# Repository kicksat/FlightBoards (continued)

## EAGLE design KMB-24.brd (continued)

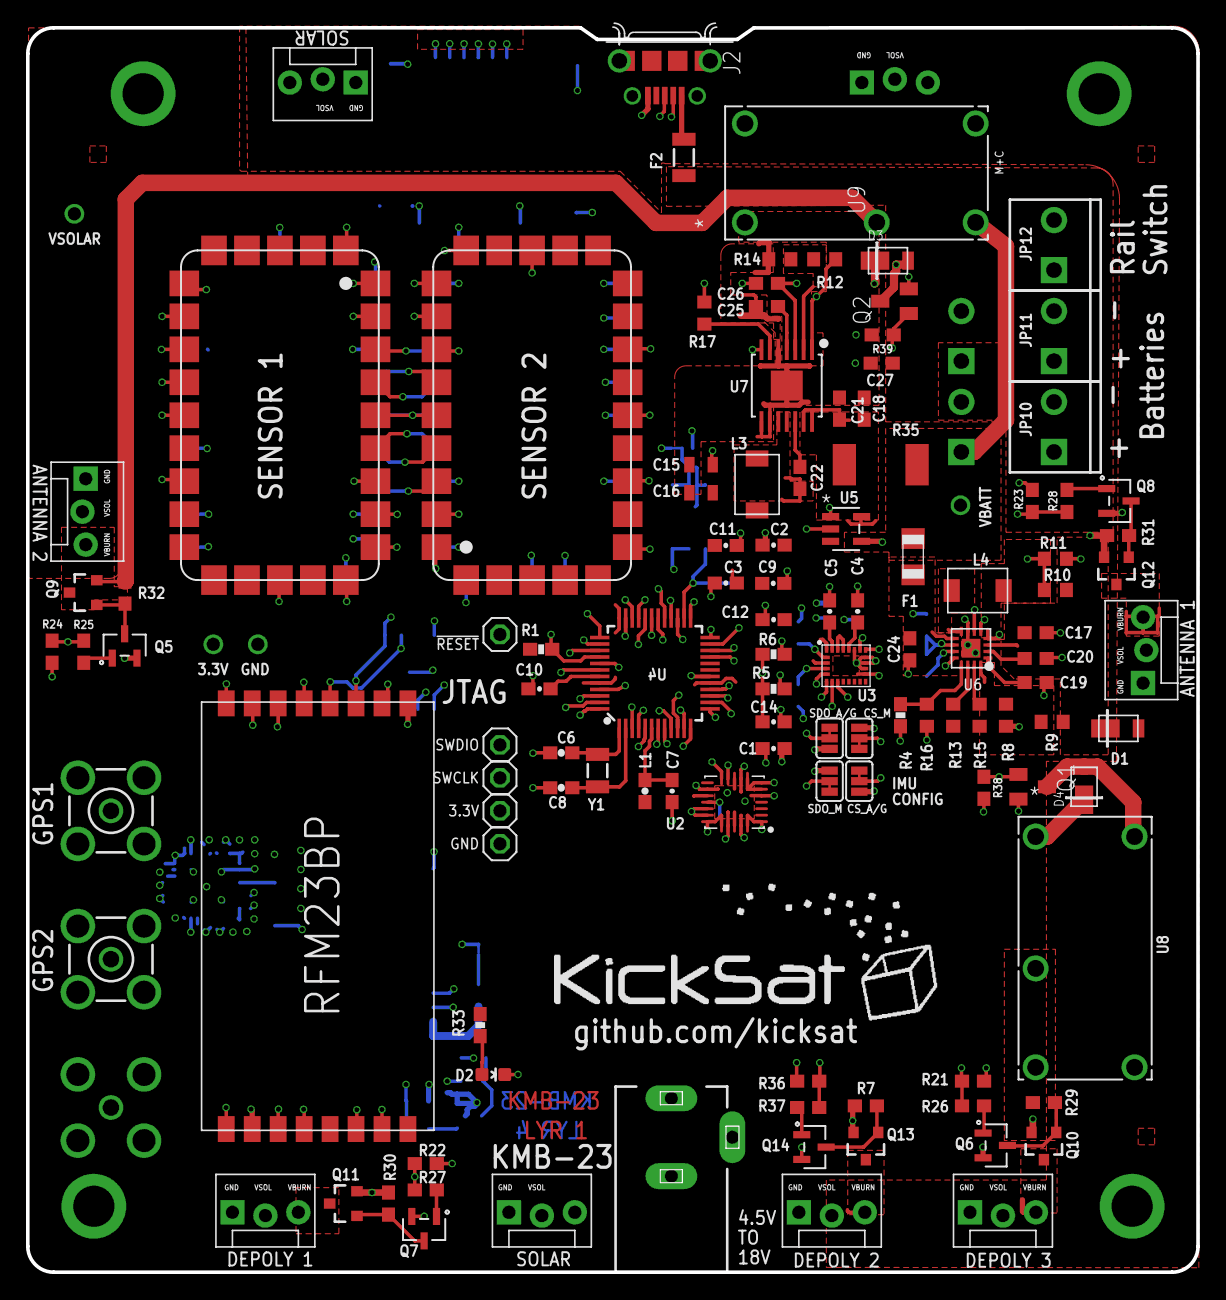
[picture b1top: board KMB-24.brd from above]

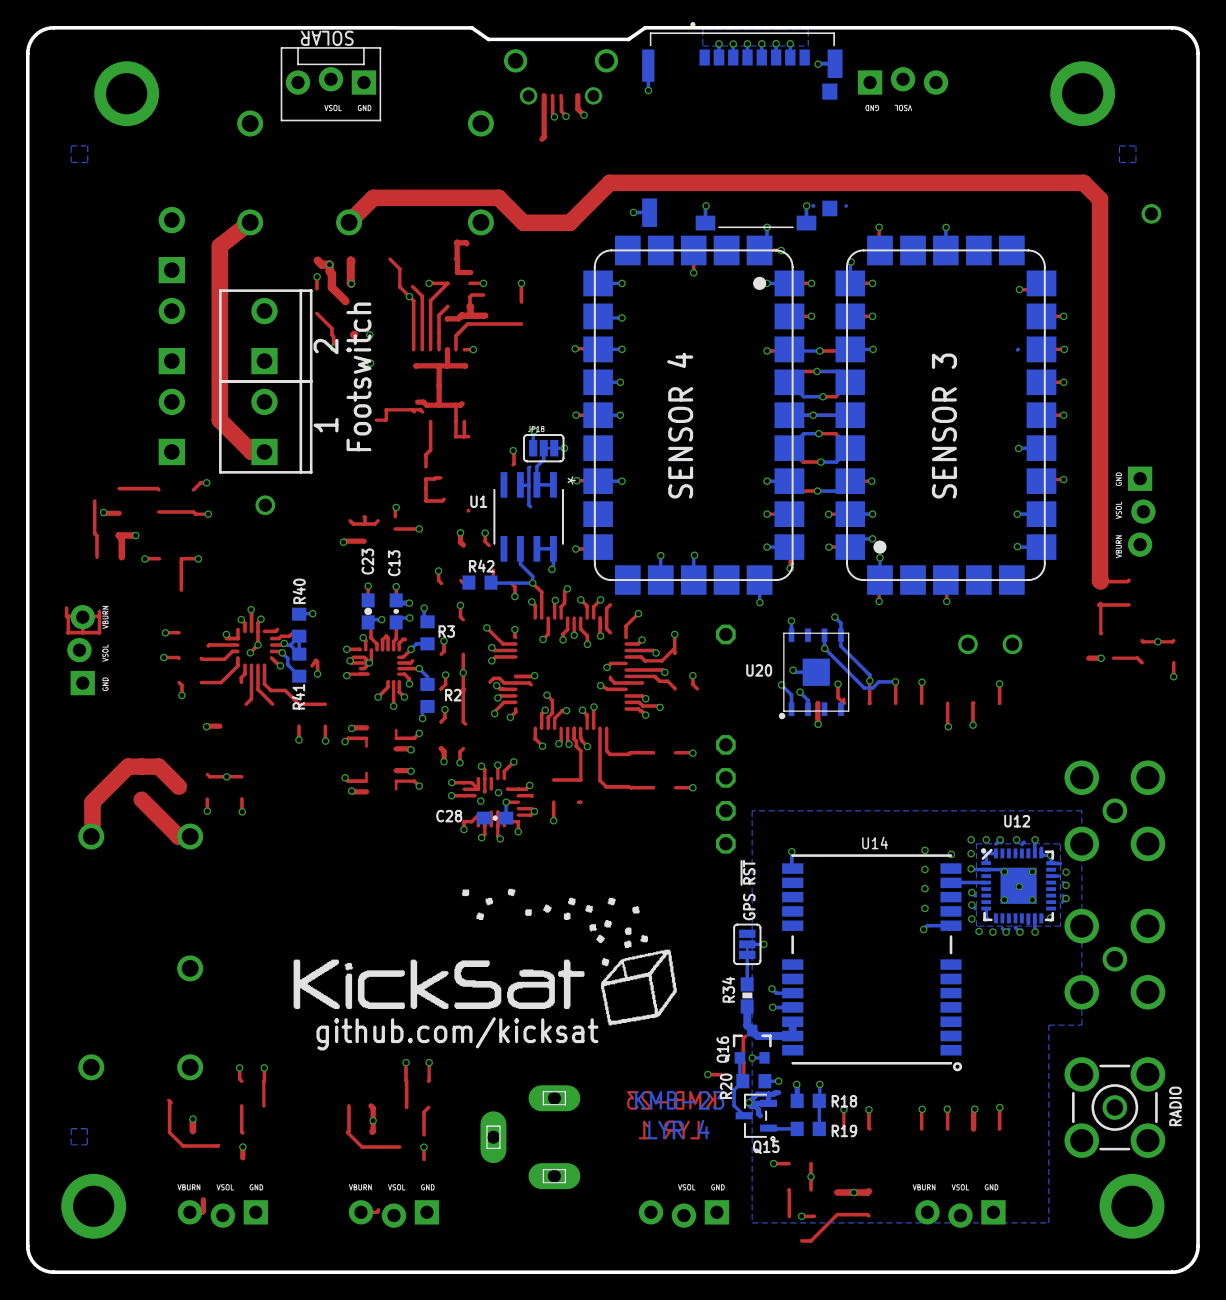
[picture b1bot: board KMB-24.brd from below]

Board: 4 copper layers, 90.2 x 95.9 mm, 148 parts (28 on the bottom side), 106 nets.

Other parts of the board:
L5: KICKSAT_LOGO

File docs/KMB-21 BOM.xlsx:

OSH ORDER 2018-06-04 |  |  | KMB-21.sch at 6/6/2018 5:23 PM
 |  |  |  |  |  | (DK 2018-04-05) | (2*2.1 rounded) | (DK 2018-06-07)
Qty | Value | Device | Package | Parts | Description | Inventory | Total Needed | New Order | Comments
3 | 22uF | 22UF-0805-6.3V-20% | 805 | C15, C16, C24 | 22ÂµF ceramic capacitors | 6 | 13 | 15
4 | 10uF | 10UF-0603-6.3V-20% | 603 | C1, C17, C18, C21 | 10.0ÂµF ceramic capacitors | 95 | 17
3 | 2.2uF | 2.2UF-0603-10V-20% | 603 | C19, C20, C27 | 2.2ÂµF ceramic capacitors | 98 | 13
12 | 0.1uF | 0.1UF-25V(+80/-20%)(0603) | 0603-CAP | C2, C3, C5, C7, C9, C10, C11, C12, C13, C14, C22, C23 | CAP-00810 | 85 | 50
1 | 3.3nF | 3.3NF-0603-100V-10% | 603 | C25 | 3.3nF ceramic capacitors | 8 | 4
1 | 1.0uF | 1.0UF-0603-16V-10% | 603 | C26 | 1ÂµF ceramic capacitors | 98 | 4
1 | 10nF | 10NF/10000PF-50V-10%(0603) | 0603-CAP | C4 | CAP-00867 | 99 | 4
2 | 15pF | 15PF-50V-5%(0603) | 0603-CAP@1 | C6, C8 | CAP-07881 | 98 | 8
1 | DFLS130L | DFLS130L | PWRDI-123 | D1 |  | 9 | 4
1 | GREEN | LED-GREEN0603 | LED-0603 | D2 | Various green LEDs | 0 | 4 | 10
1 | 1206L200 | PTCFUSE1206 | 1206 | F1 | PTC Fuse | 9 | 4
1 | 500mA | PTCSMD | PTC-1206 | F2 | Resettable Fuse PTC | 9 | 4
1 | 503182-1852 | 503182-1852 | MOLEX_503182-1852 | J1 | Conn Micro SD Card M 8 POS 1.09mm Solder RA SMD Embossed T/R 0.5A/Contact | 0 | 4 | 10
1 | 10118194-0001LF | 10118194-0001LF | FRAMATOME_10118194-0001LF | J2 | Conn Micro USB Type B RCP 5 POS 0.65mm Solder RA SMD 5 Terminal 1 Port T/R | 0 | 4 | 25
1 | DCJ0303 | DCJ0303 | DCJ0303 | J3 | DC POWER JACK | 0 | 4 | 10
5 | M023.5MM_LOCK | M023.5MM_LOCK | SCREWTERMINAL-3.5MM-2_LOCK | JP10, JP11, JP12, JP13, JP16 | Standard 2-pin 0.1" header. Use with | 45 | 21
7 |  | M03POLAR_LOCK | MOLEX-1X3_LOCK | JP5, JP6, JP8, JP9, JP14, JP15, JP17 | Header 3 | 100 | 29
1 | FB - 30Ohm | INDUCTOR0603 | 603 | L1 | Inductors | 8 | 4
1 | 3.3uH | IND1812 | 1812 | L3 |  | 2 | 4 | 0 | Decent inductors are restricted on digikey? Need to go to Mouser?
1 | 56uH | IND1812 | 1812 | L4 |  | 4 | 4
7 | IRLML2803 | IRLML2803TRPBF | SOT-23 | Q1, Q2, Q3, Q5, Q6, Q7, Q8 |  | 5 | 29 | 50
5 | IRLML5103 | MOSFET-PCHANNEL | SOT23-3 | Q4, Q9, Q10, Q11, Q12 | Generic PMOSFET | 4 | 21 | 50
8 | 10K | 10KOHM-1/10W-1%(0603)0603 | 0603-RES | R1, R4, R18, R21, R22, R23, R24, R34 | RES-00824 | 0 | 34 | 100
1 | 330K | R-US_R0603 | R0603 | R10 | RESISTOR, American symbol | 99 | 4
1 | 43K | R-US_R0603 | R0603 | R11 | RESISTOR, American symbol | 99 | 4
1 | 73.2K | R-US_R0603 | R0603 | R12 | RESISTOR, American symbol | 0 | 4 | 20
1 | 470k | R-US_R0603 | R0603 | R13 | RESISTOR, American symbol | 99 | 4
1 | 22.1k | R-US_R0603 | R0603 | R14 | RESISTOR, American symbol | 0 | 4 | 20
1 | 6.04K | R-US_R0603 | R0603 | R16 | RESISTOR, American symbol | 99 | 4
8 | 4.7k | R-US_R0603 | R0603 | R2, R3, R15, R19, R25, R26, R27, R28 | RESISTOR, American symbol | 0 | 34 | 100
1 | 3.3K | R-US_R0603 | R0603 | R20 | RESISTOR, American symbol | 99 | 4
6 | 100k | RESISTOR0603 | 603 | R8, R17, R29, R30, R31, R32 | Generic Resistor Package | 0 | 25 | 100
1 | 330 | 330OHM1/10W1%(0603) | 0603-RES | R33 | RES-00818 | 0 | 4 | 100
1 | 2.5000000000000001E-2 | R-US_R2512 | R2512 | R35 | RESISTOR, American symbol | 0 | 4 | 5
1 | 110K | 10KOHM-1/10W-1%(0603)0603 | 0603-RES | R5 | RES-00824 | 99 | 4
1 | 316K | 10KOHM-1/10W-1%(0603)0603 | 0603-RES | R6 | RES-00824 | 99 | 4
1 | 40.9K | R-US_R0603 | R0603 | R9 | RESISTOR, American symbol | 0 | 4 | 100
1 | MAX706R | MAX708RESA-T | SO8 | U1 |  | 0 | 4 | 5
1 | EP2W+ | EP2W+ | QFN32-5X5MM | U12 |  | 0 | 4 | 0
1 | RFM23BP | RFM23BP | RFM23BP | U13 | HopeRF RFM23BP | 0 | 4 | 0
1 | S1216V8 | S1216V8 | S1216_24PIN_PACKAGE | U14 |  | 0 | 4 | 0
1 | MR25H40 | MR25H40 | DFN-8 | U2 |  | 0 | 4 | 2 | Expensive
1 | LSM9DS1 | LSM9DS1 | LGA24-8X4 | U3 | LSM9DS1 3D accelerometer, gyroscope & magnetometer | 9 | 4
1 | ATSAMD21G-A | ATSAMD21G-A | TQFP-48 | U4 | Atmel SAMD21G SMART ARM-Based Microcontroller | 8 | 4
1 | MAX4372TEUK+T | MAX4372TEUK+T | 21-0057F | U5 |  | 8 | 4
1 | LTC4121-4.2 | LTC4121-4.2 | QFN-16-PAD | U6 |  | 4 | 4
1 | TPS54226PWPRPWP14_2P31X2P46-L | TPS54226PWPRPWP14_2P31X2P46-L | PWP14_2P31X2P46-L | U7 |  | 6 | 4
2 | PE014006 | PE014005 | RELAY5-PE_CO | U8, U9 |  | 0 | 8 | 10
3 | BU-SMA-V | BU-SMA-V | BU-SMA-V | X1, X2, X3 | FEMALE SMA CONNECTOR | 7 | 13 | 0
1 | 32.768kHz | CRYSTAL3.2X1.5MM | CRYSTAL-SMD-3.2X1.5MM | Y1 | Various standard crystals. Proven footprints. | 9 | 4
NON PCB ITEMS
3 | 4GB | S304TLN7B-U1000-3 |  |  | Flash Memory Card, MicroSDHC Card, UHS-1, Class 10, 4 GB, U331 Series | 0 | 1 | 0 | 56 ea from Newark http://www.newark.com/delkin-devices/s304tln7b-u1000-3/memory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

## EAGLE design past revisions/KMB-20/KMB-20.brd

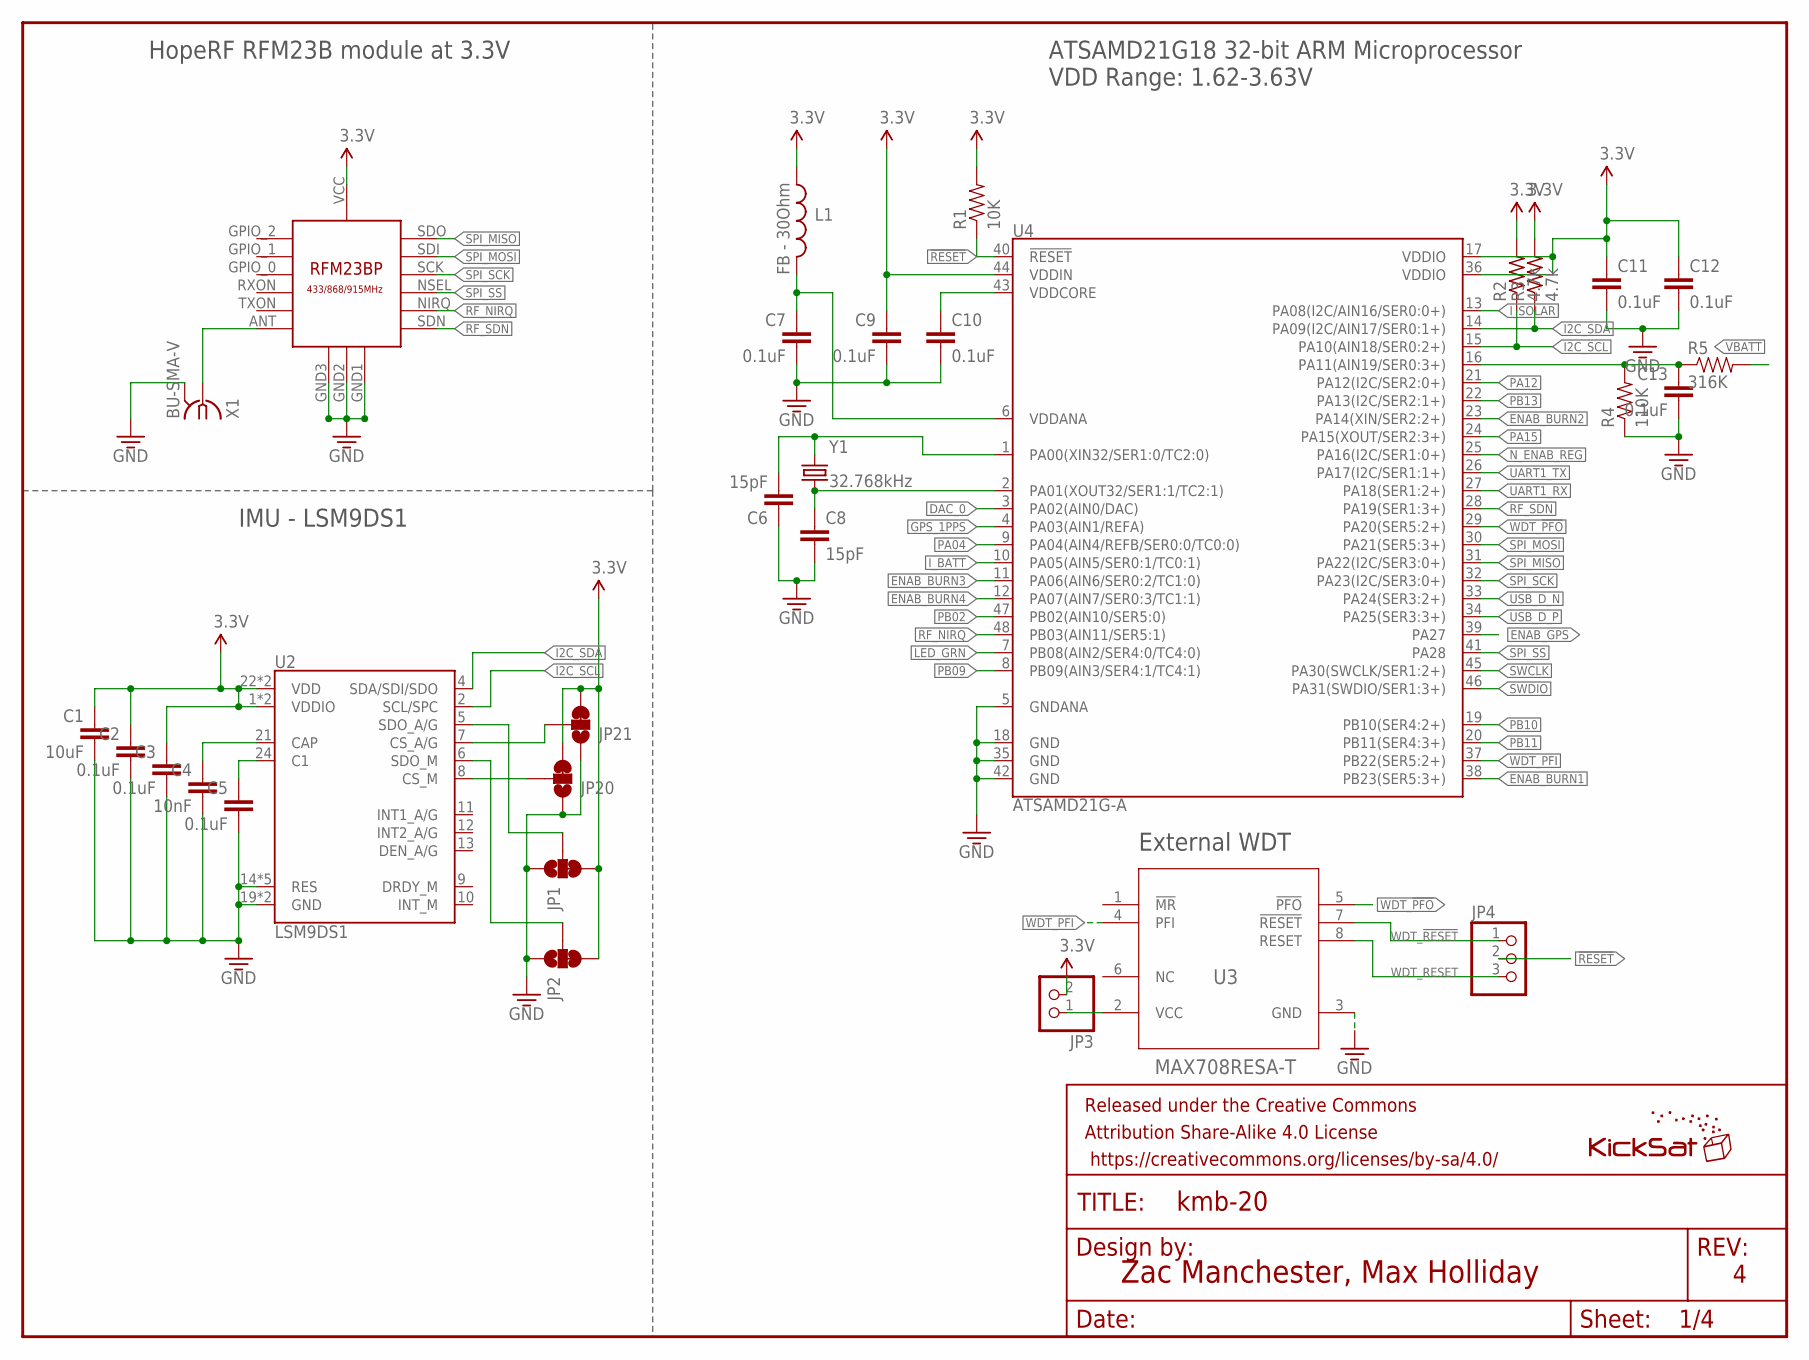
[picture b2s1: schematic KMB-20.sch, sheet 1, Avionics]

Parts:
C1: 10uF; 0603-CAP
C2, C3, C5, C7, C9, C10, C11, C12, C13: 0.1uF; 0603-CAP
C4: 10nF; 0603-CAP
C6, C8: 15pF; 0603-CAP@1
FRAME1: FRAME-LETTER; CREATIVE_COMMONS
JP1, JP2, JP20, JP21: JUMPER-PAD-3-2OF3_NC_BY_TRACE_SMALL; PAD-JUMPER-3-2OF3_NC_BY_TRACE_YES_SILK_FULL_BOX
JP3: PINHD-1X2; 1X02
JP4: PINHD-1X3; 1X03
L1: FB - 30Ohm; 0603
L2: KICKSAT_LOGO
R1: 10K; 0603-RES
R2, R3: 4.7k; R0603
R4: 110K; 0603-RES
R5: 316K; 0603-RES
U1: RFM23BP
U2: LSM9DS1; LGA24-8X4
U3: MAX708RESA-T; SO8
U4: ATSAMD21G-A; TQFP-48
X1: BU-SMA-V
Y1: 32.768kHz; CRYSTAL-SMD-3.2X1.5MM

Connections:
3.3V: C1.1, C2.1, C3.1, C9.1, C11.1, C12.1, JP1.3, JP2.3, JP3.2, JP20.3, JP21.3, L1.1, R1.2, R2.2, R3.2, U1.VCC, U2.1 (VDDIO), U2.3 (VDDIO), U2.22 (VDD), U2.23 (VDD), U4.17 (VDDIO), U4.36 (VDDIO), U4.44 (VDDIN); also elsewhere on the board
!RESET: JP4.2, R1.1, U4.40 (!RESET!); also elsewhere on the board
DAC_0: U4.3 (PA02(AIN0/DAC)); also elsewhere on the board
ENAB_BURN1: U4.38 (PB23(SER5:3+)); also elsewhere on the board
ENAB_BURN2: U4.23 (PA14(XIN/SER2:2+)); also elsewhere on the board
ENAB_BURN3: U4.11 (PA06(AIN6/SER0:2/TC1:0)); also elsewhere on the board
ENAB_BURN4: U4.12 (PA07(AIN7/SER0:3/TC1:1)); also elsewhere on the board
ENAB_GPS: U4.39 (PA27); also elsewhere on the board
GND: C1.2, C2.2, C3.2, C4.2, C5.2, C6.1, C7.2, C8.2, C9.2, C10.2, C11.2, C12.2, C13.2, JP1.1, JP2.1, JP20.1, JP21.1, R4.1, U1.GND1, U1.GND2, U1.GND3, U2.14 (RES), U2.15 (RES), U2.16 (RES), U2.17 (RES), U2.18 (RES), U2.19 (GND), U2.20 (GND), U3.3 (GND), U4.5 (GNDANA), U4.18 (GND), U4.35 (GND), U4.42 (GND), X1.2, X1.3 (2), X1.4 (2), X1.5 (2); also elsewhere on the board
GPS_1PPS: U4.4 (PA03(AIN1/REFA)); also elsewhere on the board
I2C_SCL: R2.1, U2.2 (SCL/SPC), U4.15 (PA10(AIN18/SER0:2+)); also elsewhere on the board
I2C_SDA: R3.1, U2.4 (SDA/SDI/SDO), U4.14 (PA09(I2C/AIN17/SER0:1+)); also elsewhere on the board
I2C_SDOA/G: JP1.2, U2.5 (SDO_A/G)
I_BATT: U4.10 (PA05(AIN5/SER0:1/TC0:1)); also elsewhere on the board
I_SOLAR: U4.13 (PA08(I2C/AIN16/SER0:0+)); also elsewhere on the board
LED_GRN: U4.7 (PB08(AIN2/SER4:0/TC4:0)); also elsewhere on the board
unnamed: C4.1, U2.21 (CAP)
unnamed: C5.1, U2.24 (C1)
unnamed: JP3.1, U3.2 (VCC)
unnamed: C7.1, L1.2, U4.6 (VDDANA)
unnamed: U1.ANT, X1.1
unnamed: JP2.2, U2.6 (SDO_M)
unnamed: JP20.2, U2.8 (CS_M)
unnamed: JP21.2, U2.7 (CS_A/G)
unnamed: C6.2, U4.1 (PA00(XIN32/SER1:0/TC2:0)), Y1.P$2 (2)
unnamed: C8.1, U4.2 (PA01(XOUT32/SER1:1/TC2:1)), Y1.P$1 (1)
unnamed: C13.1, R4.2, R5.1, U4.16 (PA11(AIN19/SER0:3+))
N_ENAB_REG: U4.25 (PA16(I2C/SER1:0+)); also elsewhere on the board
PA04: U4.9 (PA04(AIN4/REFB/SER0:0/TC0:0))
PA12: U4.21 (PA12(I2C/SER2:0+)); also elsewhere on the board
PA15: U4.24 (PA15(XOUT/SER2:3+))
PB02: U4.47 (PB02(AIN10/SER5:0)); also elsewhere on the board
PB09: U4.8 (PB09(AIN3/SER4:1/TC4:1)); also elsewhere on the board
PB10: U4.19 (PB10(SER4:2+)); also elsewhere on the board
PB11: U4.20 (PB11(SER4:3+)); also elsewhere on the board
PB13: U4.22 (PA13(I2C/SER2:1+))
RF_NIRQ: U1.NIRQ, U4.48 (PB03(AIN11/SER5:1))
RF_SDN: U1.SDN, U4.28 (PA19(SER1:3+))
SPI_MISO: U1.SDO, U4.31 (PA22(I2C/SER3:0+))
SPI_MOSI: U1.SDI, U4.30 (PA21(SER5:3+))
SPI_SCK: U1.SCK, U4.32 (PA23(I2C/SER3:0+))
SPI_SS: U1.NSEL, U4.41 (PA28)
SWCLK: U4.45 (PA30(SWCLK/SER1:2+)); also elsewhere on the board
SWDIO: U4.46 (PA31(SWDIO/SER1:3+)); also elsewhere on the board
UART1_RX: U4.27 (PA18(SER1:2+)); also elsewhere on the board
UART1_TX: U4.26 (PA17(I2C/SER1:1+)); also elsewhere on the board
USB_D_N: U4.33 (PA24(SER3:2+)); also elsewhere on the board
USB_D_P: U4.34 (PA25(SER3:3+)); also elsewhere on the board
VBATT: R5.2; also elsewhere on the board
VDDCORE3: C10.1, U4.43 (VDDCORE)
WDT_!PFO: U3.5 (!PFO), U4.29 (PA20(SER5:2+))
WDT_!RESET: JP4.1, U3.7 (!RESET)
WDT_PFI: U3.4 (PFI), U4.37 (PB22(SER5:2+))
WDT_RESET: JP4.3, U3.8 (RESET)

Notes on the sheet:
Zac Manchester, Max Holliday
ATSAMD21G18 32-bit ARM Microprocessor VDD Range: 1.62-3.63V
HopeRF RFM23B module at 3.3V
IMU - LSM9DS1
External WDT

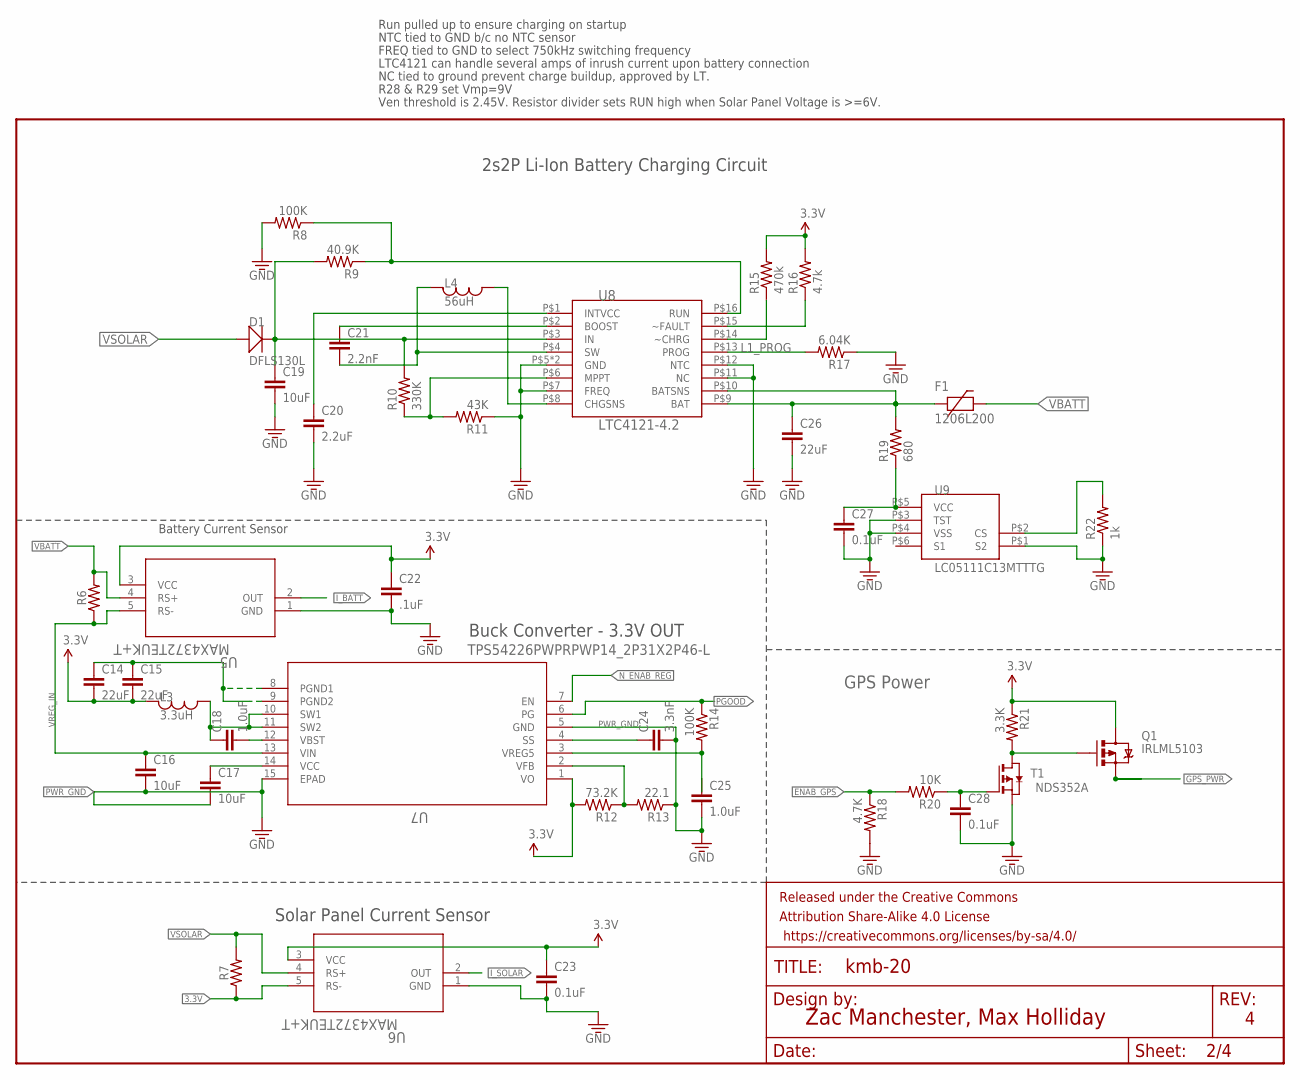
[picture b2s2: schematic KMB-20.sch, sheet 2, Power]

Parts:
C14, C15: 22uF; 0805
C16, C17, C19: 10uF; 0603
C18, C25: 1.0uF; 0603
C20: 2.2uF; 0603
C21: 2.2nF; 0603
C22: .1uF; 0603-CAP@1
C23, C27, C28: 0.1uF; 0603
C24: 3.3nF; 0603
C26: 22uF; 0603
D1: DFLS130L; PWRDI-123
F1: 1206L200; 1206
FRAME2: FRAME-LETTER; CREATIVE_COMMONS
L3: 3.3uH; 1812
L4: 56uH; 1812
Q1: IRLML5103; SOT23-3
R6, R7: 0603
R8, R14: 100K; R0603
R9: 40.9K; R0603
R10: 330K; R0603
R11: 43K; R0603
R12: 73.2K; R0603
R13: 22.1; R0603
R15: 470k; R0603
R16: 4.7k; R0603
R17: 6.04K; R0603
R18: 4.7K; R0603
R19: 680; R0603
R20: 10K; R0603
R21: 3.3K; R0603
R22: 1k; R0603
T1: NDS352A; SOT-23
U5, U6: MAX4372TEUK+T; 21-0057F
U7: TPS54226PWPRPWP14_2P31X2P46-L; PWP14_2P31X2P46-L
U8: LTC4121-4.2; QFN-16-PAD
U9: LC05111C13MTTTG; WDFN6

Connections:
3.3V: C14.2, C15.2, C22.1, C23.1, L3.P$1, Q1.3 (D), R7.1, R12.2, R15.2, R16.2, R21.1, U5.3 (VCC), U6.3 (VCC), U6.5 (RS-), U7.1 (VO); also elsewhere on the board
ENAB_GPS: R18.1, R20.2; also elsewhere on the board
GND: C19.2, C20.2, C22.2, C23.2, C26.2, C27.2, C28.2, R8.2, R11.1, R17.1, R18.2, R22.1, T1.2 (S), U5.1 (GND), U6.1 (GND), U8.P$5 (GND), U8.P$7 (FREQ), U8.P$11 (NC), U8.P$12 (NTC), U8.P$17 (GND), U9.P$1 (S2), U9.P$3 (TST), U9.P$4 (VSS); also elsewhere on the board
GPS_PWR: Q1.2 (S); also elsewhere on the board
I_BATT: U5.2 (OUT); also elsewhere on the board
I_SOLAR: U6.2 (OUT); also elsewhere on the board
L1_CHG: R8.1, R9.1, U8.P$16 (RUN)
L1_FAULTN: R16.1, U8.P$15 (~FAULT)
L1_PROG: R17.2, U8.P$13 (PROG)
LION1: C26.1, F1.1, R19.2, U8.P$9 (BAT), U8.P$10 (BATSNS)
unnamed: C18.1, L3.P$2, U7.10 (SW1), U7.11 (SW2)
unnamed: C28.1, R20.1, T1.3 (G)
unnamed: Q1.1 (G), R21.2, T1.1 (D)
unnamed: C18.2, U7.12 (VBST)
unnamed: C21.2, L4.P$1, U8.P$4 (SW)
unnamed: C21.1, U8.P$2 (BOOST)
unnamed: C20.1, U8.P$1 (INTVCC)
unnamed: R10.1, R11.2, U8.P$6 (MPPT)
unnamed: L4.P$2, U8.P$8 (CHGSNS)
unnamed: R15.1, U8.P$14 (~CHRG)
unnamed: C27.1, R19.1, U9.P$5 (VCC)
unnamed: C17.1, U7.14 (VCC)
unnamed: R22.2, U9.P$2 (CS)
unnamed: C25.1, R14.2, U7.3 (VREG5)
unnamed: C24.1, U7.4 (SS)
unnamed: R12.1, R13.2, U7.2 (VFB)
N_ENAB_REG: U7.7 (EN); also elsewhere on the board
PGOOD: R14.1, U7.6 (PG)
PWR_GND: C14.1, C15.1, C16.2, C17.2, C24.2, C25.2, R13.1, U7.5 (GND), U7.8 (PGND1), U7.9 (PGND2), U7.15 (EPAD)
VBATT: F1.2, R6.2, U5.4 (RS+); also elsewhere on the board
VREG_IN: C16.1, R6.1, U5.5 (RS-), U7.13 (VIN)
VSOLAR: D1.A, R7.2, U6.4 (RS+); also elsewhere on the board
VSOLAR_IN: C19.1, D1.C, R9.2, R10.2, U8.P$3 (IN)

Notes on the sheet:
Solar Panel Current Sensor
Battery Current Sensor
Zac Manchester, Max Holliday
GPS Power
FREQ tied to GND to select 750kHz switching frequency
R28 & R29 set Vmp=9V
2s2P Li-Ion Battery Charging Circuit
Run pulled up to ensure charging on startup
NTC tied to GND b/c no NTC sensor
LTC4121 can handle several amps of inrush current upon battery connection
NC tied to ground prevent charge buildup, approved by LT.
Ven threshold is 2.45V. Resistor divider sets RUN high when Solar Panel Voltage is >=6V.
Buck Converter - 3.3V OUT

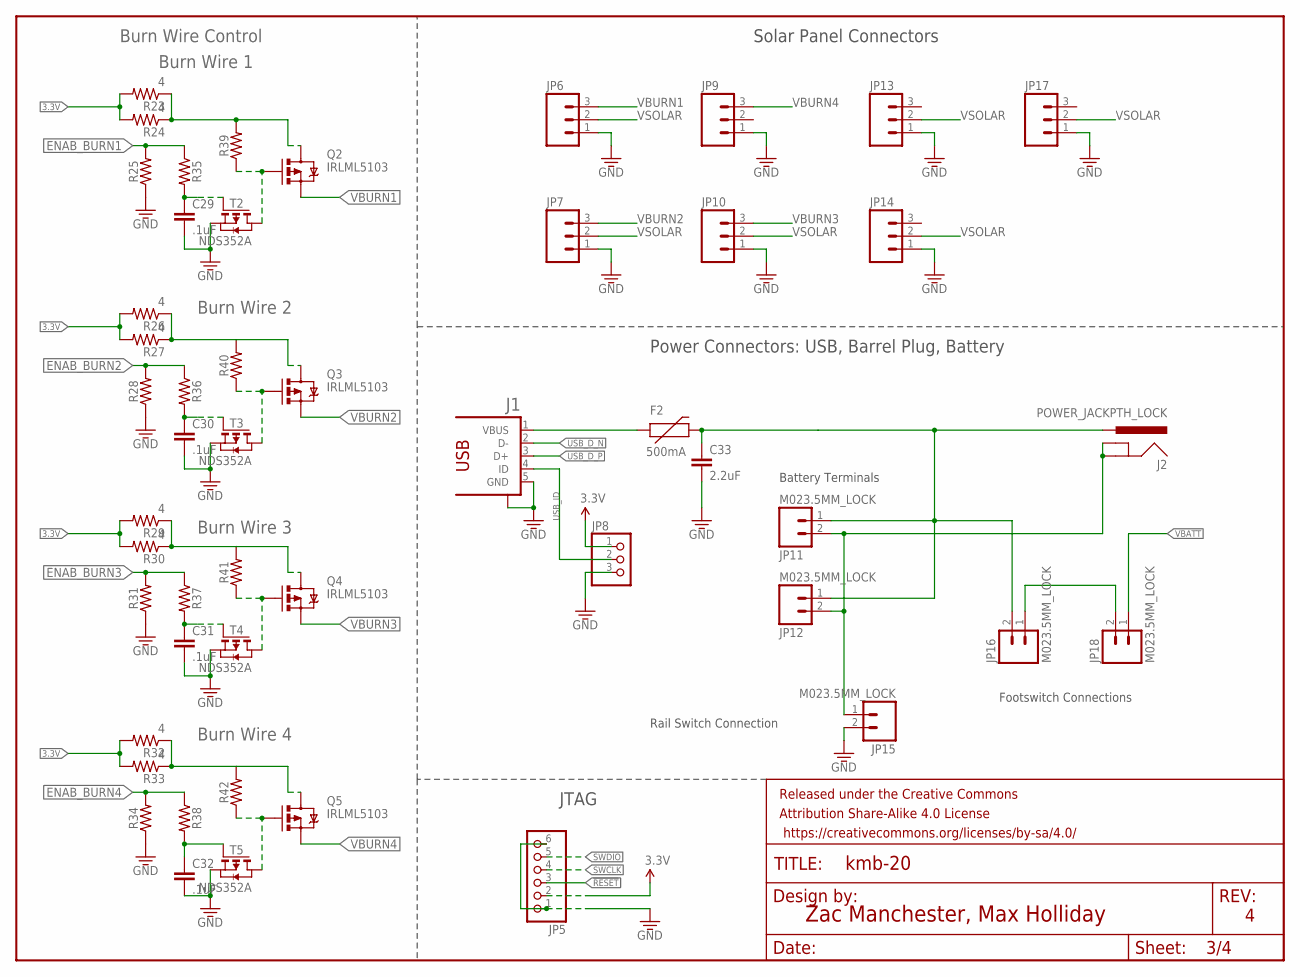
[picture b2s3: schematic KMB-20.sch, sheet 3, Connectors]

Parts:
C29, C30, C31, C32: .1uF; 0603-CAP@1
C33: 2.2uF; 0603
F2: 500mA; PTC-1206
FRAME3: FRAME-LETTER; CREATIVE_COMMONS
J1: 1981584-1
J2: POWER_JACKPTH_LOCK; POWER_JACK_PTH_LOCK
JP5: PINHD-1X6; 1X06
JP6, JP7, JP9, JP10, JP13, JP14, JP17: M03POLAR_LOCK; MOLEX-1X3_LOCK
JP8: PINHD-1X3; 1X03
JP11, JP12, JP15, JP16, JP18: M023.5MM_LOCK; SCREWTERMINAL-3.5MM-2_LOCK
Q2, Q3, Q4, Q5: IRLML5103; SOT23-3
R23, R24, R26, R27, R29, R30, R32, R33: 4; R0603
R25, R28, R31, R34, R35, R36, R37, R38, R39, R40, R41, R42: 0603
T2, T3, T4, T5: NDS352A; SOT-23

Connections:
3.3V: JP5.2, JP8.1, R23.2, R24.2, R26.2, R27.2, R29.2, R30.2, R32.2, R33.2; also elsewhere on the board
!RESET: JP5.3; also elsewhere on the board
ENAB_BURN1: R25.2, R35.1; also elsewhere on the board
ENAB_BURN2: R28.2, R36.1; also elsewhere on the board
ENAB_BURN3: R31.2, R37.1; also elsewhere on the board
ENAB_BURN4: R34.2, R38.1; also elsewhere on the board
GND: C29.2, C30.2, C31.2, C32.2, C33.2, J1.5 (GND), J1.S1, JP5.1, JP5.6, JP6.1, JP7.1, JP8.3, JP9.1, JP10.1, JP13.1, JP14.1, JP15.2, JP17.1, R25.1, R28.1, R31.1, R34.1, T2.2 (S), T3.2 (S), T4.2 (S), T5.2 (S); also elsewhere on the board
unnamed: JP16.1, JP18.2
unnamed: C30.1, R36.2, T3.3 (G)
unnamed: Q2.1 (G), R39.1, T2.1 (D)
unnamed: C31.1, R37.2, T4.3 (G)
unnamed: F2.1, J1.1 (VBUS)
unnamed: Q3.1 (G), R40.1, T3.1 (D)
unnamed: J2.GND, J2.GNDBREAK, JP11.2, JP12.2, JP15.1
unnamed: C29.1, R35.2, T2.3 (G)
unnamed: C32.1, R38.2, T5.3 (G)
unnamed: Q4.1 (G), R41.1, T4.1 (D)
unnamed: Q5.1 (G), R42.1, T5.1 (D)
SWCLK: JP5.4; also elsewhere on the board
SWDIO: JP5.5; also elsewhere on the board
USB_D_N: J1.2 (D-); also elsewhere on the board
USB_D_P: J1.3 (D+); also elsewhere on the board
USB_ID: J1.4 (ID), JP8.2
VBATT: C33.1, F2.2, J2.PWR, JP11.1, JP12.1, JP16.2, JP18.1; also elsewhere on the board
VBURN1: JP6.3, Q2.2 (S)
VBURN2: JP7.3, Q3.2 (S)
VBURN3: JP10.3, Q4.2 (S)
VBURN4: JP9.3, Q5.2 (S)
VBURN_IN: Q2.3 (D), Q3.3 (D), Q4.3 (D), Q5.3 (D), R23.1, R24.1, R26.1, R27.1, R29.1, R30.1, R32.1, R33.1, R39.2, R40.2, R41.2, R42.2
VSOLAR: JP6.2, JP7.2, JP10.2, JP13.2, JP14.2, JP17.2; also elsewhere on the board

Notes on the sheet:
Footswitch Connections
Solar Panel Connectors
Battery Terminals
Rail Switch Connection
Zac Manchester, Max Holliday
JTAG
Power Connectors: USB, Barrel Plug, Battery
Burn Wire 1
Burn Wire Control
Burn Wire 2
Burn Wire 3
Burn Wire 4

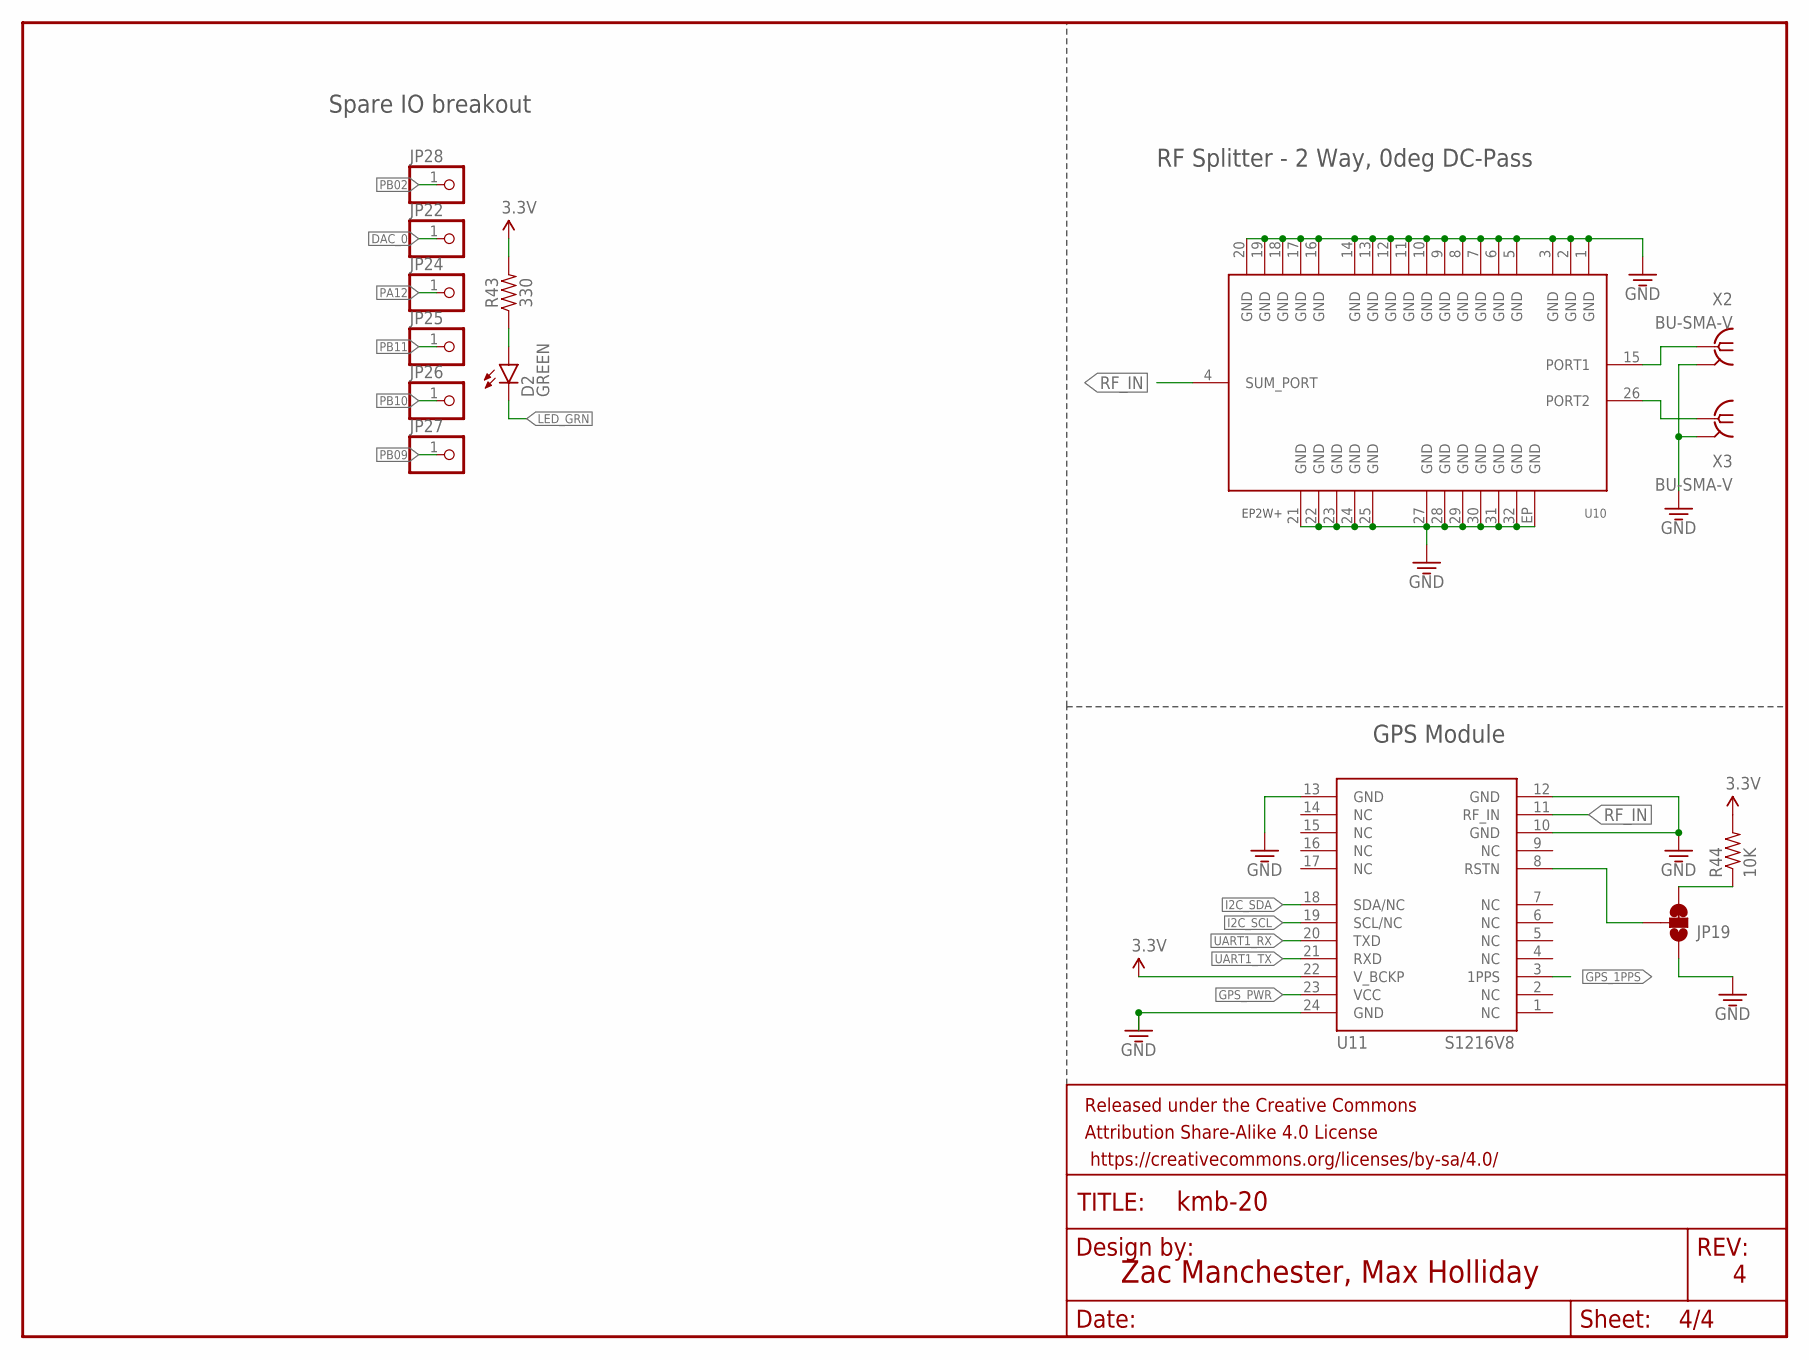
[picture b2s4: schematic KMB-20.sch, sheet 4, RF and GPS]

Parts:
D2: GREEN; LED-0603
FRAME4: FRAME-LETTER; CREATIVE_COMMONS
JP19: JUMPER-PAD-3-2OF3_NC_BY_TRACE_SMALL; PAD-JUMPER-3-2OF3_NC_BY_TRACE_YES_SILK_FULL_BOX
JP22, JP24, JP25, JP26, JP27, JP28: PINHD-1X1; 1X01
R43: 330; 0603-RES
R44: 10K; 0603-RES
U10: EP2W+; QFN32-5X5MM
U11: S1216V8; S1216_24PIN_PACKAGE
X2, X3: BU-SMA-V

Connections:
3.3V: R43.2, R44.2, U11.22 (V_BCKP); also elsewhere on the board
DAC_0: JP22.1; also elsewhere on the board
GND: JP19.1, U10.1 (GND), U10.2 (GND), U10.3 (GND), U10.5 (GND), U10.6 (GND), U10.7 (GND), U10.8 (GND), U10.9 (GND), U10.10 (GND), U10.11 (GND), U10.12 (GND), U10.13 (GND), U10.14 (GND), U10.16 (GND), U10.17 (GND), U10.18 (GND), U10.19 (GND), U10.20 (GND), U10.21 (GND), U10.22 (GND), U10.23 (GND), U10.24 (GND), U10.25 (GND), U10.27 (GND), U10.28 (GND), U10.29 (GND), U10.30 (GND), U10.31 (GND), U10.32 (GND), U10.EP (GND), U11.10 (GND), U11.12 (GND), U11.13 (GND), U11.24 (GND), X2.2, X2.3 (2), X2.4 (2), X2.5 (2), X3.2, X3.3 (2), X3.4 (2), X3.5 (2); also elsewhere on the board
GPS_1PPS: U11.3 (1PPS); also elsewhere on the board
GPS_PWR: U11.23 (VCC); also elsewhere on the board
I2C_SCL: U11.19 (SCL/NC); also elsewhere on the board
I2C_SDA: U11.18 (SDA/NC); also elsewhere on the board
LED_GRN: D2.C; also elsewhere on the board
unnamed: D2.A, R43.1
unnamed: JP19.2, U11.8 (RSTN)
unnamed: U10.15 (PORT1), X2.1
unnamed: U10.26 (PORT2), X3.1
unnamed: JP19.3, R44.1
PA12: JP24.1; also elsewhere on the board
PB02: JP28.1; also elsewhere on the board
PB09: JP27.1; also elsewhere on the board
PB10: JP26.1; also elsewhere on the board
PB11: JP25.1; also elsewhere on the board
RF_IN: U10.4 (SUM_PORT), U11.11 (RF_IN)
UART1_RX: U11.20 (TXD); also elsewhere on the board
UART1_TX: U11.21 (RXD); also elsewhere on the board

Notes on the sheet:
GPS Module
RF Splitter - 2 Way, 0deg DC-Pass
Zac Manchester, Max Holliday
Spare IO breakout
